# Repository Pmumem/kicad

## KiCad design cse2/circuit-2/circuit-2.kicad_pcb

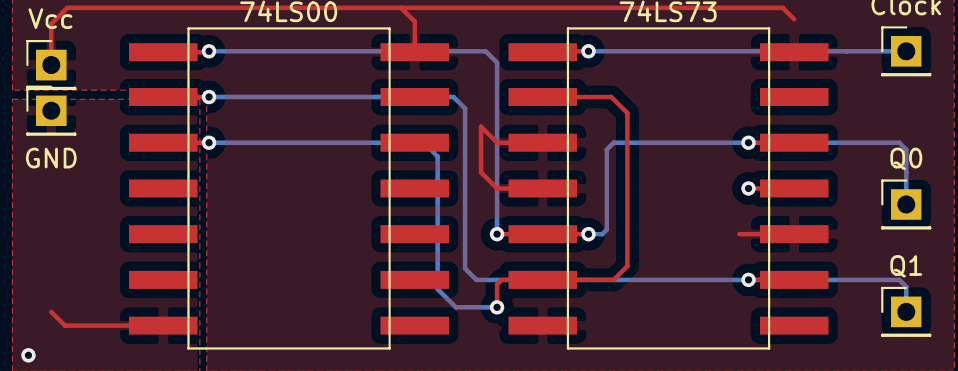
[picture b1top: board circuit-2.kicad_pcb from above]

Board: 2 copper layers, 7 parts (0 on the bottom side), 6 nets.

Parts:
74LS00: 74LS00; DIP-14-SMD
74LS73: 74LS73; DIP-14-SMD
Clock: Conn_01x01_Male; PinHeader_1x01_P2.54mm_Vertical
GND: Conn_01x01_Male; PinHeader_1x01_P2.54mm_Vertical
Q0, Q1: Conn_01x01_Male; PinHeader_1x01_P2.54mm_Vertical
Vcc: Conn_01x01_Male; PinHeader_1x01_P2.54mm_Vertical

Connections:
CK: 74LS73.1, Clock.1
GND: 74LS00.7, 74LS73.11, GND.1
unnamed: 74LS00.1, 74LS73.5, 74LS73.12, Q0.1
unnamed: 74LS00.2, 74LS73.9, Q1.1
unnamed: 74LS00.3, 74LS73.2, 74LS73.6
VCC: 74LS00.14, 74LS73.3, 74LS73.4, 74LS73.7, 74LS73.10, 74LS73.14, Vcc.1

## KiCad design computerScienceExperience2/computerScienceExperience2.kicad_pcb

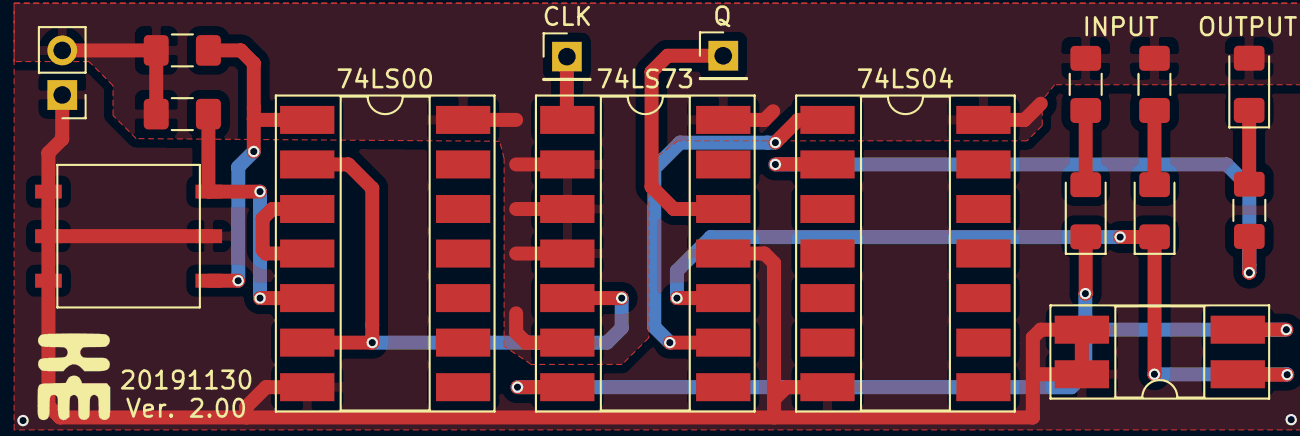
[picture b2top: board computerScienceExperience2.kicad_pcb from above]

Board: 2 copper layers, 16 parts (0 on the bottom side), 15 nets.

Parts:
74LS00: 74HC00; DIP-14_W8.89mm_SMDSocket_LongPads
74LS04: 74HC04; DIP-14_W8.89mm_SMDSocket_LongPads
74LS73: 74HC73; DIP-14_W8.89mm_SMDSocket_LongPads
CLK: Conn_01x01_Male; PinHeader_1x01_P2.54mm_Vertical
D1, D2, D3: LED; LED_1206_3216Metric_Pad1.42x1.75mm_HandSolder
J1: Conn_01x02; PinHeader_1x02_P2.54mm_Vertical
Q: Conn_01x01_Male; PinHeader_1x01_P2.54mm_Vertical
R1, R2, R3, R4, R5: 470; R_1206_3216Metric_Pad1.42x1.75mm_HandSolder
SW1: SW_Push_SPDT; TL2285
SW2: SW_DIP_x02; DIP-4_W8.89mm_SMDSocket_LongPads

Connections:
/CLK: 74LS00.2, 74LS00.6, 74LS73.5
/GND: 74LS00.7, 74LS04.7, 74LS73.11, J1.1, SW1.2, SW2.3, SW2.4
/INPUT_J: 74LS73.7, D1.1, SW2.2
/INPUT_K: 74LS73.10, D2.1, SW2.1
/OUTPUT_PULSE: 74LS73.12, Q.1
/OUTPUT_Q: 74LS04.1, 74LS73.9
/PULSE: 74LS73.1, CLK.1
/Vcc: 74LS00.14, 74LS04.14, 74LS73.2, 74LS73.3, 74LS73.4, 74LS73.6, 74LS73.14, D3.2, J1.2, R1.1, R2.1, R3.1, R4.1
unnamed: D1.2, R3.2
unnamed: D2.2, R4.2
unnamed: D3.1, R5.1
unnamed: 74LS00.1, R1.2, SW1.1
unnamed: 74LS00.5, R2.2, SW1.3
unnamed: 74LS04.2, R5.2
unnamed: 74LS00.3, 74LS00.4

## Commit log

2019-11-11 computerScienceExperience2 ver1.10
2019-11-27 computerScienceExperience2 ver1.20
2019-11-27 add compornent
2019-11-30 computerScienceExperence2 ver. 2.00
2019-11-30 edit footprint
2020-09-14 add circuit-2
2020-09-18 complete circuit-2
2020-09-24 add gerber
2020-09-24 remove tmp
